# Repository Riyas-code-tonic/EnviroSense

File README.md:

<div align="center">

<table>
<tr>

<td>

</td>

<td>

# 𝓔𝓷𝓿𝓲𝓻𝓸𝑺𝒆𝒏𝒔𝒆

</td>

</tr>
</table>

### Smart IoT Weather & Air Quality Monitoring System

*Turning real-time environmental data into meaningful insights.*

</div>

# 🌿 Overview

**EnviroSense** is a smart IoT platform that transforms environmental sensing into an interactive monitoring experience. Built around the ESP32 and the BME680 environmental sensor, the system continuously measures temperature, humidity, atmospheric pressure, and air quality before securely transmitting the data to the cloud.

Rather than limiting sensor readings to a serial monitor, EnviroSense combines cloud connectivity, a responsive web dashboard, local OLED visualization, intelligent email alerts, and power-efficient firmware to create a complete end-to-end monitoring solution. The project demonstrates how embedded systems, cloud communication, and modern web technologies can seamlessly work together to make environmental information accessible from anywhere.

---

# 🌐 Live Dashboard

Experience the deployed dashboard here:

### **https://enviro-sense-delta.vercel.app**

> *Live readings are available whenever the ESP32 device is connected and publishing data.*

---

## 📑 Table of Contents

- [Overview](#-overview)
- [Live Dashboard](#-live-dashboard)
- [About the Project](#-about-the-project)
- [Key Features](#-key-features)
- [How EnviroSense Works](#-how-envirosense-works)
- [Technologies Used](#-technologies-used)
- [Hardware](#-hardware)
- [PCB Design](#-pcb-design)
- [Challenges](#-challenges)
- [What We Learned](#-what-we-learned)
- [Future Scope](#-future-scope)
- [Contributors](#-contributors)

---

# 📖 About the Project

Environmental conditions constantly change, yet understanding those changes often requires specialised equipment or complex monitoring systems. EnviroSense was developed to bridge that gap by providing a compact, affordable, and intelligent platform capable of collecting, transmitting, and visualising environmental data in real time.

At its core, the ESP32 communicates with the BME680 sensor to measure temperature, humidity, atmospheric pressure, and gas resistance. The collected readings are published to Adafruit IO using the MQTT protocol, allowing them to be securely accessed through a custom-built web dashboard from virtually anywhere.

To make the system practical beyond simple monitoring, EnviroSense also incorporates an OLED display that provides live sensor readings directly on the device, enabling users nearby to instantly view environmental conditions without opening the dashboard. An integrated email alert system further enhances usability by automatically notifying users whenever predefined environmental thresholds are exceeded, ensuring that important changes never go unnoticed.

Together, these components transform EnviroSense from a simple sensor project into a complete IoT monitoring solution that combines embedded systems, cloud services, and web technologies into one cohesive platform.

---

## ⚡ Key Features

- Real-time environmental monitoring (Temperature, Humidity, Pressure & Air Quality)
- MQTT-based cloud communication
- Adafruit IO cloud integration
- Interactive web dashboard
- Automated email alert system
- Power optimization using Deep Sleep
- OLED display for local monitoring
- Responsive interface for desktop and mobile
- Secure cloud-based data visualization

---

# 🧠 How EnviroSense Works

EnviroSense follows a complete IoT workflow where sensing, communication, visualization, and notification work together to provide continuous environmental monitoring.

The BME680 sensor periodically measures temperature, humidity, atmospheric pressure, and gas resistance. These readings are collected by the ESP32, where they are processed, formatted, and prepared for transmission. Once connected to Wi-Fi, the ESP32 publishes the latest environmental data to Adafruit IO using the lightweight MQTT protocol, making the information available over the internet in real time.

The custom-built web dashboard retrieves these values from the cloud and updates the visual interface automatically. Interactive gauges and graphs allow users to monitor changing environmental conditions from any device without requiring direct access to the hardware.

For users who are physically near the device, the integrated OLED display provides an immediate view of the latest sensor readings. This enables quick local monitoring even when internet access or the dashboard is unavailable, making the system useful in both remote and on-site environments.

EnviroSense also includes an automated email notification system designed to improve responsiveness. Whenever monitored parameters exceed predefined threshold values, the system automatically triggers an email alert, allowing users to take timely action without continuously checking the dashboard. This makes the platform suitable for applications where immediate awareness of environmental changes is important.

To improve efficiency and reduce unnecessary power consumption, the firmware incorporates power optimization techniques such as **Deep Sleep mode**. Instead of remaining active continuously, the ESP32 periodically wakes up, collects sensor readings, transmits the data to the cloud, updates the OLED display, checks alert conditions, and then returns to a low-power sleep state. This significantly reduces energy usage and extends battery life, making EnviroSense better suited for long-term deployments in remote or battery-powered environments.

The overall workflow can be summarized as follows:

EnviroSense delivers a reliable environmental monitoring solution that remains practical for both everyday use and long-term IoT deployments.

---

# 🛠 Technologies Used

### Hardware

- ESP32 Development Board
- BME680 Environmental Sensor
- OLED Display

### Software & Cloud

- Arduino IDE
- HTML
- CSS
- JavaScript
- MQTT
- Adafruit IO
- Vercel

---

# 🔌 Hardware

The hardware combines the ESP32 with the BME680 environmental sensor to continuously monitor atmospheric conditions. An integrated OLED display allows nearby users to view live sensor readings directly from the device, while the ESP32 manages wireless communication, cloud connectivity, email notifications, and power-efficient operation within a compact embedded system.
<div align="center">

</div>

---

# 📐 PCB Design

To improve reliability and move beyond a breadboard prototype, a dedicated PCB was designed for the system. The custom PCB provides cleaner connections, better durability, and a more compact implementation, making the overall design easier to assemble, maintain, and deploy.
<div align="center">
 </div>

---

# 🚧 Challenges

Developing EnviroSense involved much more than interfacing a sensor. Integrating reliable cloud communication, designing an intuitive dashboard, implementing automated notifications, optimizing power consumption, and ensuring smooth interaction between hardware and software required continuous testing, debugging, and refinement. Overcoming these challenges helped transform the project into a stable and practical IoT solution.

---

# 🎓 What We Learned

EnviroSense provided valuable experience in designing complete IoT systems that combine embedded hardware with cloud-based applications. Throughout the project, we strengthened our understanding of sensor interfacing, MQTT communication, responsive web development, cloud deployment, PCB design, power optimization, debugging, and collaborative software development while learning how independently developed components can be integrated into a single, scalable solution.

---

# 🚀 Future Scope

Although EnviroSense already provides a comprehensive environmental monitoring solution, several enhancements can further extend its capabilities:

- Machine learning-based environmental prediction
- Mobile application support
- Historical data analytics
- Multi-device monitoring
- User authentication
- Additional environmental sensors
- Customizable alert thresholds

---

# 👨‍💻 Contributors

- **Riya Pailwan**
- **Rajnarayan Hazra**
- **Harsh Patange**

---

# ⭐ Support

If you found this project interesting, consider giving the repository a **Star ⭐**. Your support motivates us to continue improving EnviroSense and building more innovative open-source projects.

<div align="center">

Made with ❤️ using ESP32, IoT, and Web Technologies.

</div>

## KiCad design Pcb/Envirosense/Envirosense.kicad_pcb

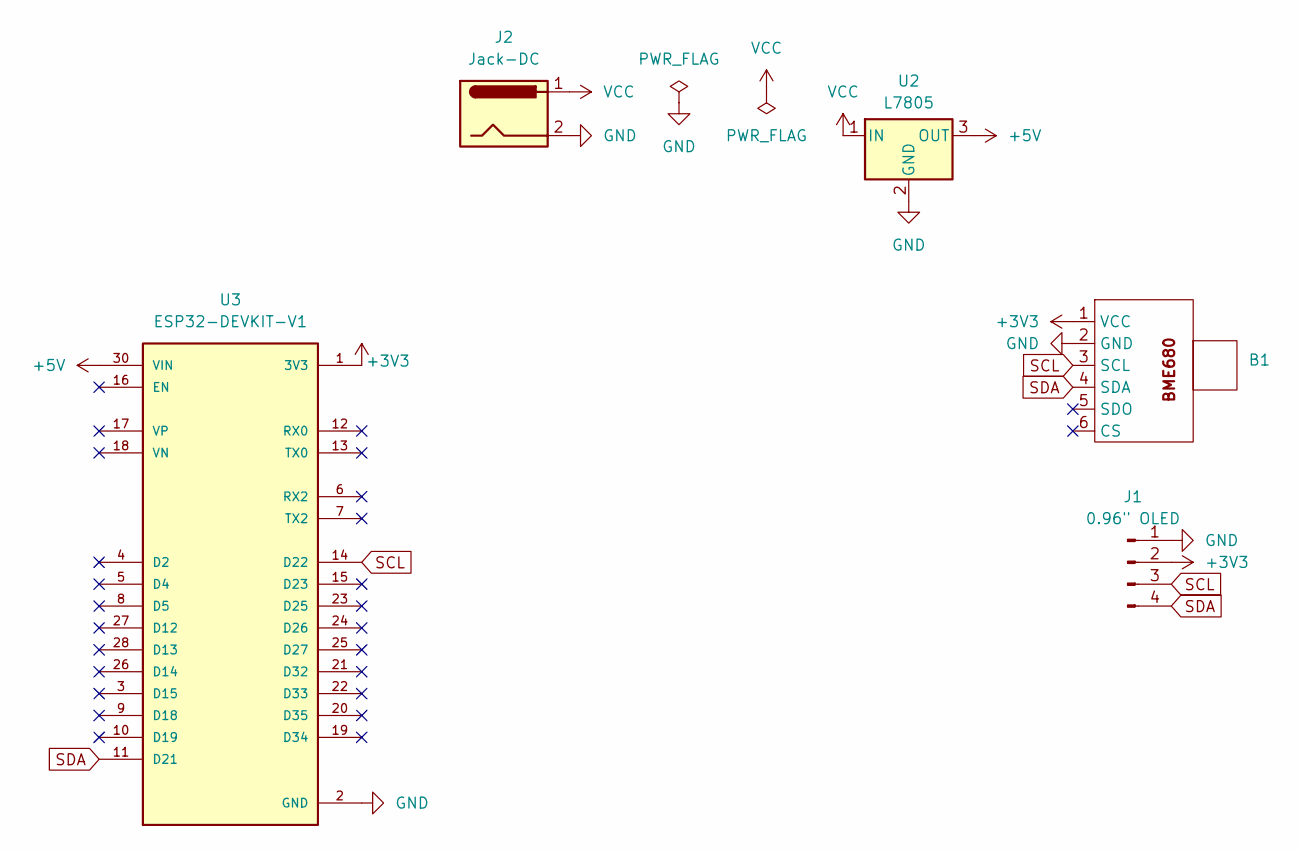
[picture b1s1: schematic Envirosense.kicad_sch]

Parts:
B1: PinHeader_1x06_P2.54mm_Vertical
J1: 0.96" OLED; PinHeader_1x04_P2.54mm_Vertical
J2: Jack-DC; BarrelJack_Horizontal
U2: L7805; TO-220-3_Vertical
U3: ESP32-DEVKIT-V1; MODULE_ESP32_DEVKIT_V1; PARTREV N/A

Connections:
+3V3: B1.1 (VCC), J1.2, U3.1 (3V3)
+5V: U2.3 (OUT), U3.30 (VIN)
GND: B1.2 (GND), J1.1, J2.2, U2.2 (GND), U3.2 (GND), U3.29 (GND)
SCL: B1.3 (SCL), J1.3, U3.14 (D22)
SDA: B1.4 (SDA), J1.4, U3.11 (D21)
VCC: J2.1, U2.1 (IN)

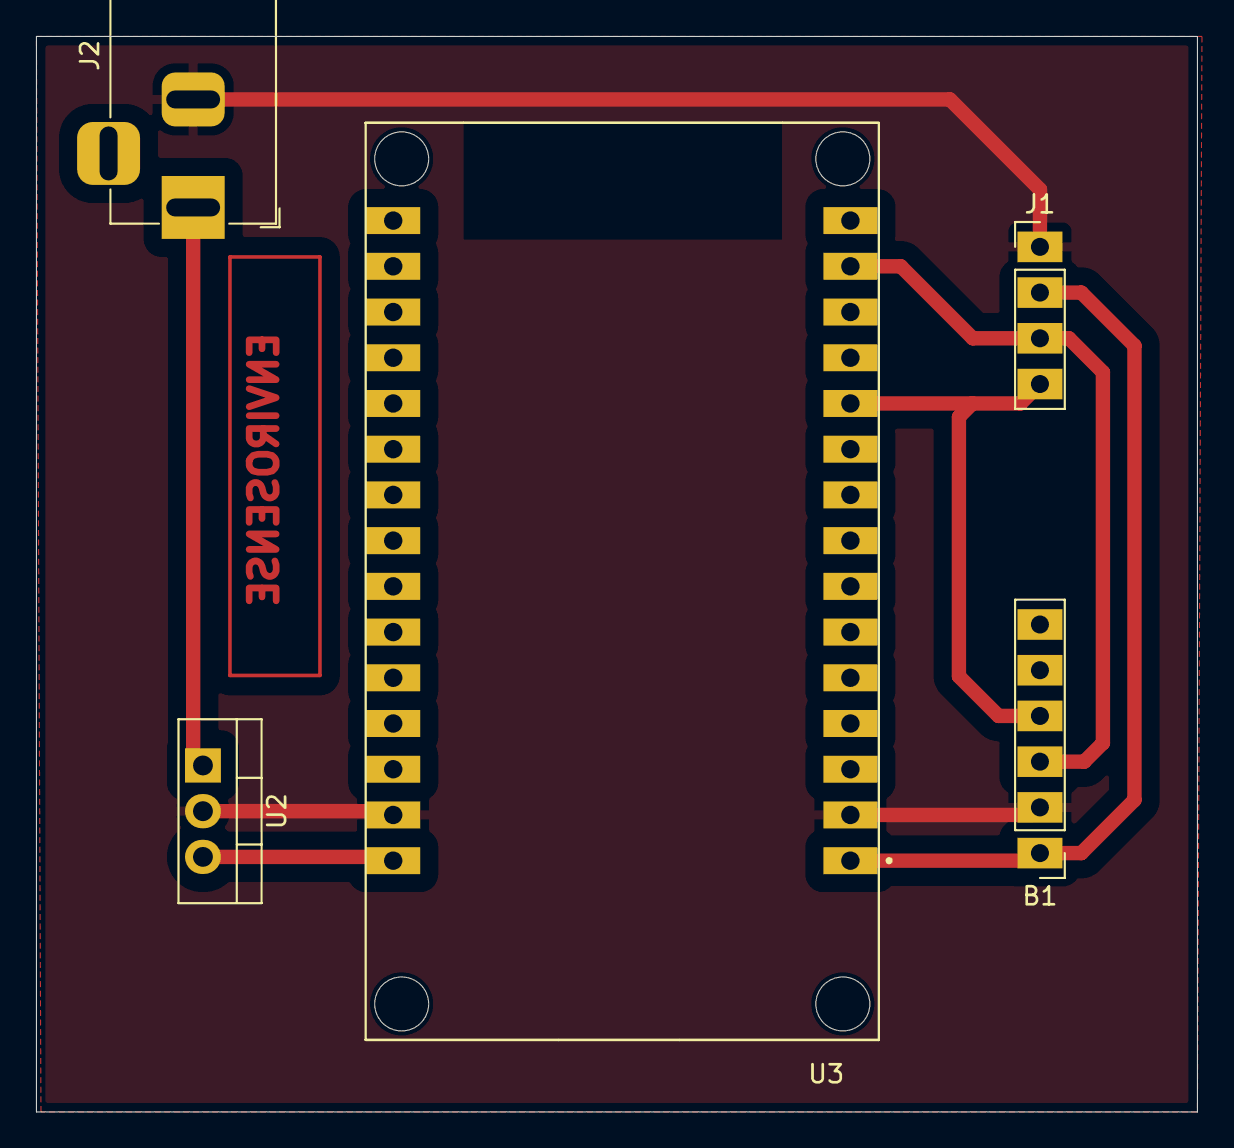
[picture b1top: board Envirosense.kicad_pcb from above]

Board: 2 copper layers, 64.5 x 59.8 mm, 5 parts (0 on the bottom side), 6 nets.

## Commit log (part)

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2026-06-16 Interface
2026-06-19 INTERFACES
2026-06-19 Added project images
2026-06-26 Added the files to code
2026-06-27 Added Breadboard Circuit image
2026-06-27 Added the PCB layout and routing pdf
